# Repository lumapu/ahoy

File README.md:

[![CC BY-NC-SA 4.0][cc-by-nc-sa-shield]][cc-by-nc-sa]
[![Ahoy Build][release-action-badge]][release-action-link] [![Ahoy Dev Build][dev-action-badge]][dev-action-link]

This work is licensed under a
[Creative Commons Attribution-NonCommercial-ShareAlike 4.0 International License][cc-by-nc-sa].

[![CC BY-NC-SA 4.0][cc-by-nc-sa-image]][cc-by-nc-sa]

[cc-by-nc-sa]: https://creativecommons.org/licenses/by-nc-sa/4.0/deed.de
[cc-by-nc-sa-image]: https://licensebuttons.net/l/by-nc-sa/4.0/88x31.png
[cc-by-nc-sa-shield]: https://img.shields.io/badge/License-CC%20BY--NC--SA%204.0-lightgrey.svg

[release-action-badge]: https://github.com/lumapu/ahoy/actions/workflows/compile_release.yml/badge.svg
[release-action-link]: https://github.com/lumapu/ahoy/actions/workflows/compile_release.yml

[dev-action-badge]: https://github.com/lumapu/ahoy/actions/workflows/compile_development.yml/badge.svg
[dev-action-link]: https://github.com/lumapu/ahoy/actions/workflows/compile_development.yml

# 🖐 Ahoy!

This repository provides hardware and software solutions for communicating with Hoymiles inverters via radio. Our system allows you to easily obtain real-time values, such as power, current, and daily energy, as well as set parameters like the power limit of your inverter to achieve zero export. You can access these functionalities through our user-friendly web interface, MQTT, or JSON. Our solutions simplify the process of monitoring and fine-tuning your solar panel system to help you achieve your goals.

## Changelog
[latest Release](https://github.com/lumapu/ahoy/blob/main/src/CHANGES.md)

[Development Version](https://github.com/lumapu/ahoy/blob/development03/src/CHANGES.md)

Table of approaches:

| Board  | MI | HM | HMS/HMT | comment | HowTo start |
| ------ | -- | -- | ------- | ------- | ---------- |
| [ESP32, C++](manual/Getting_Started.md) | ✔️ | ✔️ | ✔️ |  [create your own DTU](https://ahoydtu.de/getting_started/) |
| ESP8266, C++ | ✔️ | ✔️ | ❌ | ⚠️ not recommended for new DTU |

⚠️ **Warning: HMS-XXXXW-2T WiFi inverters are not supported. They have a 'W' in their name and a DTU serial number on its sticker**

## Getting Started
1. [Guide how to start with a ESP module](manual/Getting_Started.md)

2. [ESP Webinstaller (Edge / Chrome Browser only)](https://ahoydtu.de/web_install)

3. [Ahoy Configuration ](manual/ahoy_config.md)

## Your User Manual

* [Ahoy User_Manual](manual/User_Manual.md)

## Our Website
[https://ahoydtu.de](https://ahoydtu.de)

[Firmware Archive https://fw.ahoydtu.de](https://fw.ahoydtu.de)

## Success Stories
- [Getting the data into influxDB and visualize them in a Grafana Dashboard](https://grafana.com/grafana/dashboards/16850-pv-power-ahoy/) (thx @Carl)

## Support, Feedback, Information and Discussion
- [Discord Server (~ 7.300 Users)](https://discord.gg/WzhxEY62mB)
- [The root of development](https://www.mikrocontroller.net/topic/525778)

### Development
If you encounter any problems, use the issue tracker on Github. Provide a detailed description of the issue and consider if it is related to our software. This will help us provide effective solutions.

**Contributors are always welcome!**

### Related Projects
- [OpenDTU](https://github.com/tbnobody/OpenDTU)
  <- Our sister project ✨ for Hoymiles HM- and HMS-/HMT-series (for ESP32 only!)
- [hms-mqtt-publisher](https://github.com/DennisOSRM/hms-mqtt-publisher)
  <- a project which can handle WiFi inverters like HMS-XXXXW-2T

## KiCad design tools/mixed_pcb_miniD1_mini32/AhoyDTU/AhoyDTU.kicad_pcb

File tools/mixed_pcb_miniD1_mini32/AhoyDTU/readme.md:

small PCB to mount Wemos mini D1 or Wemos mini32, an OLED an the RF module

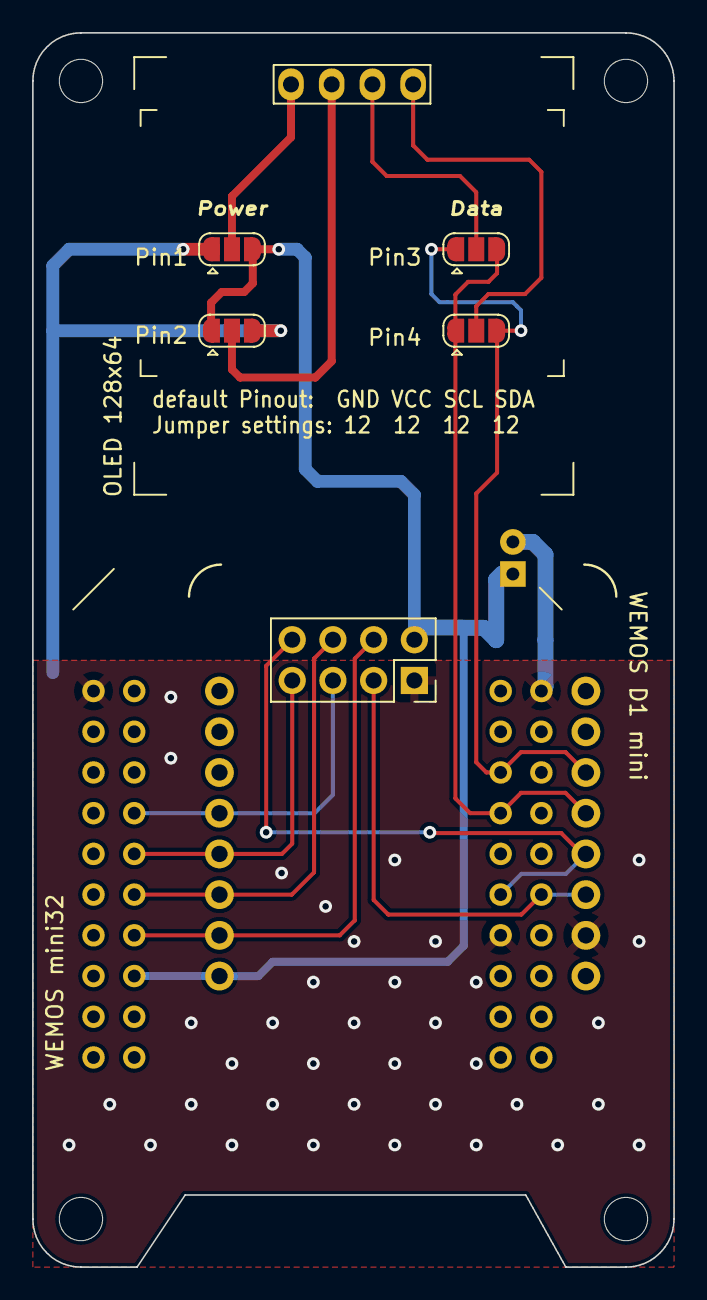
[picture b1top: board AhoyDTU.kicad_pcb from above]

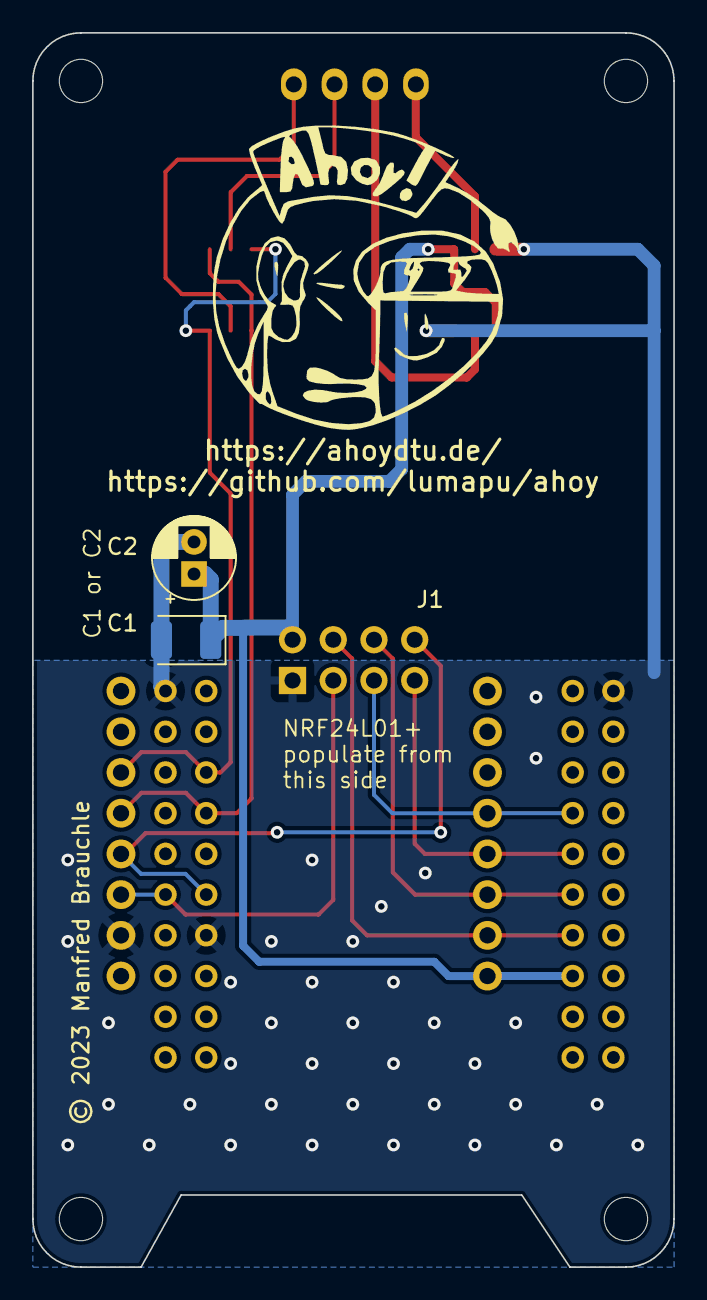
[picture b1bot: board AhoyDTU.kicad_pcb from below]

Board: 2 copper layers, 40.0 x 77.0 mm, 14 parts (2 on the bottom side), 14 nets.

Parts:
Brd1: SSD1306; 128x64OLED
C1: C_Polarized; CP_EIA-3528-21_Kemet-B
C2: C_Polarized; CP_Radial_D5.0mm_P2.00mm
H1, H2, H3, H4: MountingHole; MountingHole_2.7mm_M2.5
J1: Conn_02x04_Odd_Even; PinSocket_2x04_P2.54mm_Vertical
JP1, JP2, JP3, JP4: SolderJumper_3_Open; SolderJumper-3_P1.3mm_Open_RoundedPad1.0x1.5mm
U1: mini_esp32; ESP32_mini
U2: WeMos_D1_mini; wemos-d1-mini-with-pin-header-and-connector

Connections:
+3V3: C1.1, C2.1, J1.2, JP1.3 (B), JP2.1 (A), U1.16 (3V3), U2.8 (3.3V)
CE: J1.3, U1.32 (IO_04), U2.11 (D4)
CSN: J1.4, U1.14 (IO_05/D8), U2.7 (D8)
GND: C1.2, C2.2, J1.1, JP1.1 (A), JP2.3 (B), U1.1 (GND), U1.22 (GND), U1.33 (GND), U2.10 (GND)
IRQ: J1.8, U1.31 (IO_16/D4), U2.12 (D3)
MISO: J1.7, U1.10 (IO_19/D6), U2.5 (D6)
MOSI: J1.6, U1.12 (IO_23/D7), U2.6 (D7)
unnamed: Brd1.1 (GND), JP1.2 (C)
unnamed: Brd1.2 (VCC), JP2.2 (C)
unnamed: Brd1.3 (SCL), JP3.2 (C)
unnamed: Brd1.4 (SDA), JP4.2 (C)
SCK: J1.5, U1.8 (IO_18/D5), U2.4 (D5)
SCL: JP3.1 (A), JP4.3 (B), U1.25 (IO_22/D1/SCL), U2.14 (D1)
SDA: JP3.3 (B), JP4.1 (A), U1.27 (IO_21/D2/SDA), U2.13 (D2)

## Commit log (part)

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2024-03-15 0.8.910011-zero
2024-03-15 0.8.910012-zero
2024-03-16 0.8.94
2024-03-18 * made ethernet pinout configurable * combined common network functions into class * seperated wifi station from AP mode
2024-03-21 started ESP8266 wifi refactored platformio.ini
2024-03-21 0.8.96 * fix precision of power limit in `/live` #1517 * fix translation of `Werte ausgeben` in `settings` #1507 * add grid profile #1518
2024-03-22 Add Tibber
2024-03-22 0.8.97 * add support for newest generation of inverters with A-F in their serial number * fix NTP and sunrise / sunset * set default coordinates to the mid of Germany #1516
2024-03-22 0.8.970002-zero
2024-03-24 esp8266 works
2024-03-25 0.8.98 * fix Ethernet * modified wizard * fix github compile?
2024-03-25 0.8.98 fix compile
2024-03-26 SML add some phase
2024-03-26 0.8.99 * fix compilation of all environments
2024-03-27 0.8.970005-zero
2024-03-27 Bugfix: Negativer SetPoint
2024-03-27 Bugfix: SetLimit (kein Limit < ZEROEXPORT_GROUP_WR_LIMIT_MIN_DIFF)
2024-03-27 Bugfix: newDataAvailable ivL
2024-03-27 0.8.970007
2024-03-27 0.8.101 * updated converter scripts to include all enabled features again (redundant scan of build flags) #1534
2024-03-28 Bugfix: platformio.ini
2024-03-28 0.8.970009-zero
2024-03-30 Redesign Statemachine
2024-03-30 Add MQTT parts (publish groups)
2024-03-30 Optimize
2024-03-30 fix issue zeroexport PowerL123
2024-03-30 Update zeroExport.h - fix
    fix needed: dont continue inverter id 0
2024-03-31 Redesign
2024-03-31 Redesign, Bugfix onMqttMessage enable/disable -> init groups
2024-03-31 Timing
2024-03-31 mqtt->rssi nicht in /ch0/, mqtt->json kein YieldDay/YieldTotal einzeln
2024-03-31 Redesign, MQTT
2024-04-01 Bugfix: groupSetReboot
2024-04-01 shorten last cmt waiting time
    after last frame is received. Works, see around this discord post: https://discord.com/channels/984173303147155506/1029761098381017098/1220679912587792404
2024-04-01 MaxTemp Berechnung und Anzeige
2024-04-01 0.8.102 * fix MDNS #1538 * improved Wizard * improved MqTT on devcontrol e.g. set power limit
2024-04-01 fix: get refresh property from object
2024-04-02 0.8.103 * merge PR: fix: get refresh property from object #1552 * merge PR: fix typos and spelling in Github Issue template #1550 * merge PR: shorten last cmt waiting time #1549
2024-04-02 0.8.103 * fix cppcheck warnings * changed MqTT retained flags of some topics
2024-04-02 Add Defines for each Powermeter
2024-04-02 Bugfix: log
2024-04-03 ZE MQTT
2024-04-03 ZE log
2024-04-03 Update powermeter.h
    new function to set header http.
    New secret if statement to secure tibber password.
2024-04-03 0.8.104 * fix reboot on inverter save (ESP32) #1559 * fix NRF and Ethernet #1506
2024-04-04 ZE Bugfix log debug
2024-04-04 ZE optimize groupSetLimit
2024-04-04 0.8.105 * cleanup of `defines.h`
2024-04-04 0.8.105 * fix compile of esp32-minimal
2024-04-05 0.8.106 * fix bootloop with CMT and NRF on ESP32 #1566 #1562
2024-04-05 0.8.106 * change MqTT return value of power limit acknowledge from `boolean` to `float`. The value returned is the same as it was set to confirm reception (not the read back value)
2024-04-05 0.8.106 fix compile
2024-04-07 Update getPowermeterWattsMqtt
2024-04-08 Bugfix powermeter_dev, log
2024-04-08 0.8.107 * fix boot loop on `reboot on midnight` feature #1542, #1599, #1566, #1571
2024-04-08 0.8.107 * improved `Wizard`
2024-04-08 0.8.107 * fix serial console flag
2024-04-09 Update zeroExport.h
    format changes
2024-04-10 0.8.1030003
2024-04-11 ZE Bugfix mqtt
2024-04-11 0.8.110 * add disable retain flag #1582
2024-04-11 0.8.110 * fix ESP8266 compile
2024-04-13 Disable upload and import buttons when no file is selected
2024-04-14 some fixes, display does not work but no boot loops any more
2024-04-14 update patch
2024-04-15 removed boot loop, busy has to be MISO
2024-04-17 try to solve issue without success
2024-04-17 0.8.111 * merge PR: Disable upload and import buttons when no file is selected #1586 #1519
2024-04-18 change line endings
2024-04-19 fix total info
2024-04-22 0.8.1030004
2024-04-23 0.8.1030006
2024-04-24 0.8.1030007
2024-04-25 code cleanup
2024-04-29 0.8.114 * fix ESP8266 compile * fix history graph * fix close button color of modal windows in dark mode #1598 * fix only one total field in `/live` #1579
2024-05-01 small improvements
2024-05-02 0.8.1030009
2024-05-03 Powermeter refresh hinzugefügt
2024-05-03 0.8.115 * fix inverter communication with manual time sync #1603 * improved queue, only add new object once they not exist * added option to reset values on communication start (sunrise)
2024-05-03 0.8.115 * fixed calculation of max AC power (API, MqTT)
2024-05-05 0.8.116 * calculation of max AC power * fix counter overflow communication queue * added max inverter temperature
2024-05-08 0.8.117 * fix reboot issue #1607
2024-05-10 possible reconnect strongest wifi fix
2024-05-10 0.8.118 * possible fix reset max values #1609 * slightly improved WiFi reconnect
2024-05-11 add JS for formular Powermeter-DropDown
    show all DIVs and remove only what is not necessary
2024-05-11 0.8.103..13
2024-05-11 some notes for tibber problems & format zeroexport
2024-05-12 0.8.1030014
2024-05-14 0.8.103..15
2024-05-14 fix tibber query and timer
2024-05-15 extend JS for battery formular (dropdown)
2024-05-16 combine two for-loops into one
    waste of time with two for-loops
2024-05-17 0.8.119 * add yield day to history graph #1614
2024-05-17 0.8.119 * added script and [instructions](../manual/factory_firmware.md) how to generate factory firmware which includes predefined settings
2024-05-18 0.8.119 * untested combination of Ethernet and Wifi (Ethernet connection will cancel Wifi connection)
2024-05-18 0.8.119 * merge PR: Fix MI overnight behaviour #1626
2024-05-18 0.8.120 * fix crash if invalid serial number was set
2024-05-18 0.8.120 * fix factory generation for ESP32-S3
2024-05-18 0.8.120 * improved and fixed factory image generation * fix HMT-1800-4T number of inputs #1628
2024-05-20 0.8.121 * fix plot of history graph #1635
2024-05-20 Powermeter add getDataMAX
2024-05-21 HMT-1600/1800/2000 support
2024-05-23 0.8.122 * add button for donwloading coredump
2024-05-23 0.8.122 * fix github action
2024-05-23 0.8.122 * fix elf file rename
2024-05-23 0.8.122 * fix workflow
2024-05-29 Update RestApi.h
    remove pm_pass, for security reason
2024-05-29 Update platformio.ini for debugging
    change branch from MQTTClient to a special comit
2024-05-29 Update setup.html
    fix bug for battery_btn (need to discussed with lumapu)
2024-05-29 fix pm_pass
2024-05-29 0.8.1030018
2024-05-30 0.8.123 * fix ESP8266 static IP #1643 #1608 * update MqTT library which enhances stability
2024-05-30 0.8.123 * mention PR for MqTT Library update
2024-05-30 0.8.123 * merge PR: MQTT JSON Payload pro Kanal und total, auswählbar #1541 * add option to publish mqtt as json * publish rssi not on ch0 any more, published on `topic/rssi` * add total power to ind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
2024-05-30 0.8.123 * add environment name to filename of coredump
2024-05-30 0.8.123 * fix ESP8266 compile
2024-05-31 Update zeroExport.h
    auf DynamicJsonDocument vorbereitet
2024-05-31 remove doc.clear(); from toString()
    doc.clear(); // TODO: Entfernen wegen mqtt + webserial?
2024-05-31 0.8.1030019
2024-06-01 Update powermeter.h
    fix u8_t realm from null to zero.
2024-06-01 Update zeroExport.h
    fix battswitch, add if statement for alarm-messages
2024-06-01 Update RestApi.h
    fix parse power & add battswitch fix
2024-06-01 platformio modified
2024-06-01 0.8.1030020
2024-06-02 0.8.1230002
2024-06-03 compile_zero-export.yml
2024-06-06 0.8.124 * improved MqTT `OnMessage` (threadsafe)
2024-06-06 0.8.124 * support of HERF inverters, serial number is converted in Javascript #1425 * revert buffer size in `RestAPI` for ESP8266 #1650
2024-06-07 Add function to toggle show/hide password
2024-06-09 mobile display view without line break
2024-06-09 0.8.125 * fix ESP8266 compilation * merge PR: active_PowerLimit #1663
2024-06-12 Update pubMqtt.h - Bugfix #1673
    Ahoy reboots because MQTT receives a Topic
2024-06-12 code formatting
2024-06-14 Bugfix Inv delete not working with password protection
2024-06-21 0.8.127
2024-06-27 add read_temp_c to system + mqtt
2024-07-07 Execute ticker immediately when timeout value is 0
2024-07-11 platformio added openfusion-16MB versions for zero-export
2024-07-11 add header file
2024-07-11 mqtt redesign mit subscribe / unsubcribe der topic (Teamwork tictrick + Daniel92)
2024-07-11 0.8.1280001
2024-07-12 Bugfix für Mqtt unsubcribe/subscribe Fremdtopic
2024-07-12 wifi_init_default: netstack cb reg failed with 12308
2024-07-18 reduce update cycle of ePaper from 5 to 10 seconds
    ... and fix calls to mEpaper.fullRefresh() and mEpaper.tickerSecond() if no ePaper is configured
2024-07-26 fix (c) footer.html
2024-08-04 changed epaper interval to 15s
2024-08-04 0.8.130 * add timestamp to JSON output #1707 * restart Ahoy using MqTT #1667
2024-08-05 corrected warnings
2024-08-08 fixed define error
2024-08-09 0.8.132 * fix boot loop once no ePaper is connected #1713, #1714
2024-08-09 Ethernet + Wifi fully functional
2024-08-10 0.8.133 * Ethernet variants now support WiFi as fall back / configuration
2024-08-11 0.8.134 * redesigned `/system`
2024-08-11 0.8.135 * translated `/system` #1717
2024-08-12 0.8.136 * fix save settings for ESP32 devices #1720
2024-08-13 0.8.137 * fix storage of timezone and region #1723
2024-08-15 0.8.139 * fix reload after save for WiFi configurations (5s -> 20s)
2024-08-16 0.8.140 release * fix workflow
2024-08-16 update issue report added __pycache__ to gitignore
2024-08-16 update issue report
2024-08-16 0.8.141 * fix display IP in ePaper display (ETH or WiFi, static or DHCP) #1439
2024-08-23 fix Systeminfo
2024-08-28 0.8.142 * fix compile for ESP8266
2024-08-30 add displ_motion feature in API
2024-09-14 added comments and cleanup
2024-09-14 0.8.144 fix ESP8266 compile
2024-09-23 0.8.146 * fix reset ticker #1754 * disable MqTT second and minute ticker on network loss * converted many `std::bind` to its lambda pendant
2024-09-23 0.8.146 * fix redirect after login
2024-09-29 further improved queue
2024-09-29 0.8.147 * fixed send power limit #1757
2024-09-29 0.8.147 fix compilation
2024-10-01 Fix typos
    Fixed some German typos
2024-10-01 0.8.149 * merged: Fix minor typos #1758
2024-10-02 0.8.150 * fix nullptr exception * modified MqTT to not publish while not connected * removed patch for Webserver library - obsolete
2024-10-03 0.8.151 * don't interrupt current command by setting a new limit #1757
2024-10-03 remove reference to pkg_resource which is deprecated in python 3.12
2024-10-03 0.8.151 fix ESP8266 compilation
2024-10-04 HA discovery IP address fix, HA json output fix
2024-10-07 0.8.152 * merge: avoid using pkg_resources because it's deprecated in python 3.12 #1759 * merge: HA discovery IP address fix, HA json output fix #1760
2024-10-18 Update Getting_Started.md
    A table of features added
    https://github.com/lumapu/ahoy/issues/1734
2024-10-19 round with mathematics
2024-10-20 Update handleNTPPacket
2024-10-21 test
2024-10-22 RPI: check and repaire 'logging output' and callback function 'on_message' - add: docstrings and comments - new: MQTT (PAHO) callback function: on_connect - change: MQTT (PAHO) callback function: on_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
2025-01-27 timezone setting included
2025-03-05 0.8.154 release
2025-05-19 Always retain the LWT message
2025-05-23 Update hmDefines.h with Byte order as in HERF_1CH.cpp, HERF_2CH.cpp
    #1829 suggests to use the byte order in the RealTimeRunData response as implemented in HERF_1CH.cpp, HERF_2CH.cpp of the OpenDTU project.
    HERF_4CH.cpp uses the same byte order as HM_4CH.cpp and therefor these bytes are left unchanged.
2025-05-25 Update imagedata.h
    leave 25 pixels, i.e. 12.5 top and bottom
2025-05-28 logo 200x200 with 50 pixel white border
2025-05-28 logo 200x200 with 25 pixel white border
2025-05-30 reduced logo size, no borders, padding has to be done
    As requested by @lumapu I have reduced both logo sizes.
    I have added the display size these logos fit and the required left/right and top/bottom padding in a comment each.
    You will have to replace all occurrences of logo with logo_spiral_140x150 or implement logo_spiral_52x56 for the OLED and Nokia LCD Displays.

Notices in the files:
tools/mixed_pcb_miniD1_mini32/AhoyDTU/AhoyDTU.kicad_pcb:
© 2023 Manfred Brauchle
